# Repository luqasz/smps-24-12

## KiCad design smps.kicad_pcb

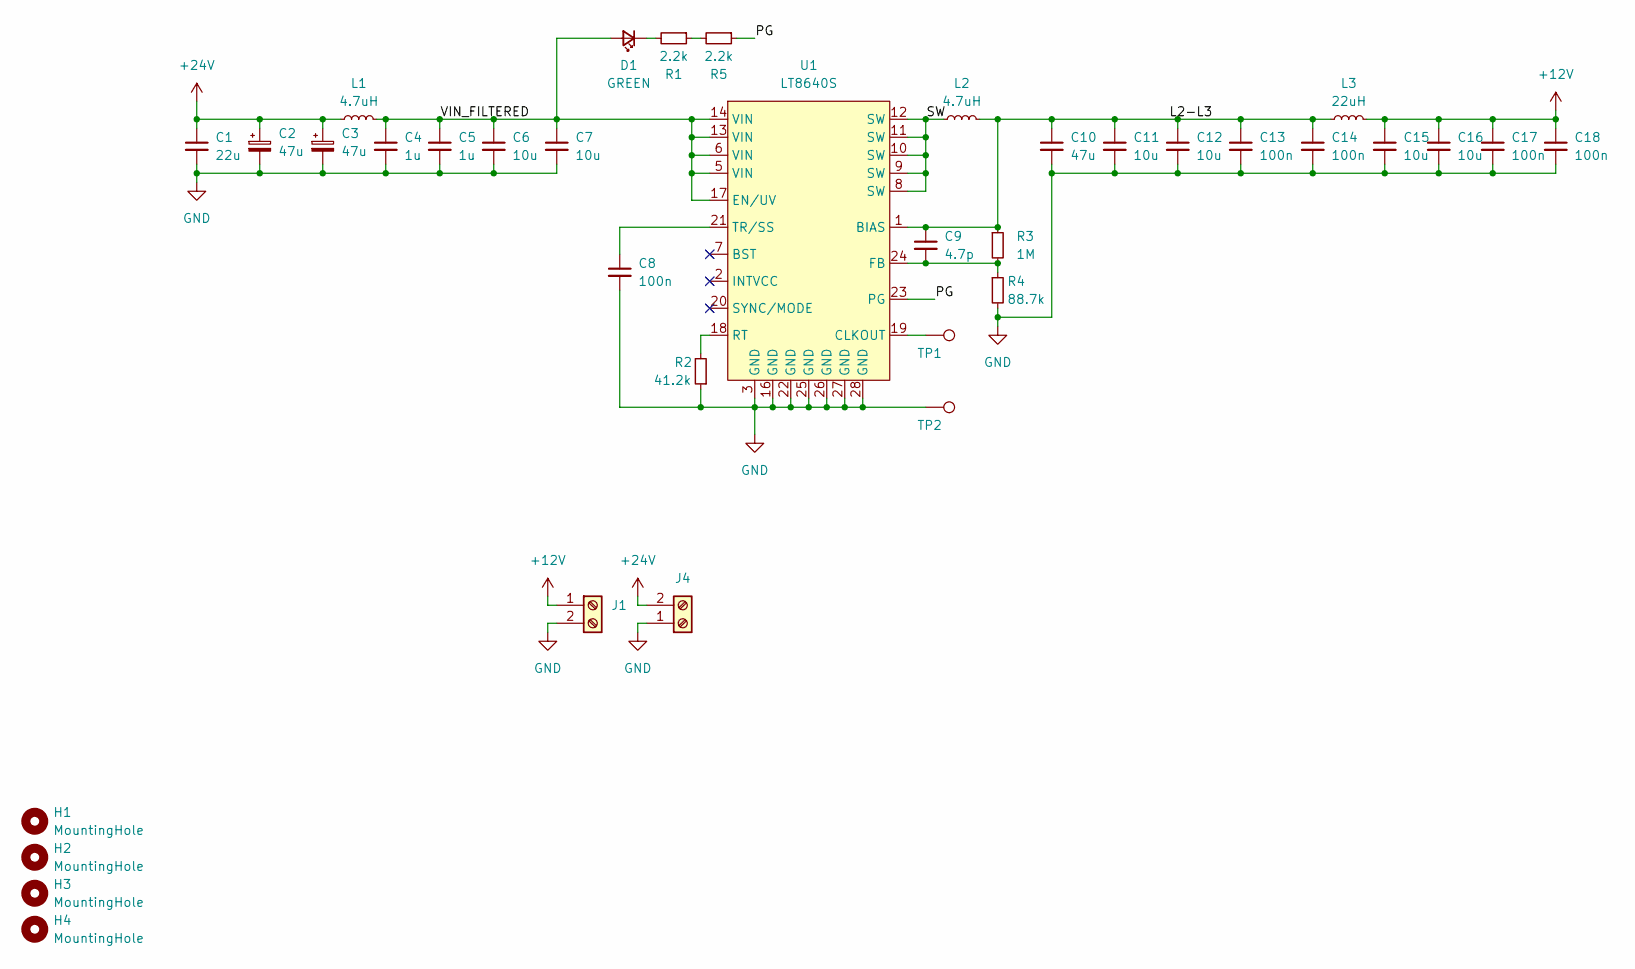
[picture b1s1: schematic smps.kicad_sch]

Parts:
C1: 22u; C_1206_3216Metric
C2, C3: 47u; CP_Elec_8x6.2
C4, C5: 1u; C_0805_2012Metric
C6, C7, C11, C12, C15, C16: 10u; C_1206_3216Metric
C8, C13, C14, C17, C18: 100n; C_0805_2012Metric
C9: 4.7p; R_0805_2012Metric
C10: 47u; C_1206_3216Metric
D1: GREEN; LED_0805_2012Metric
H1, H2, H3, H4: MountingHole; MountingHole_3.2mm_M3
J1, J4: Screw_Terminal_01x02; TerminalBlock_Phoenix_MKDS-1,5-2-5.08_1x02_P5.08mm_Horizont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
L1, L2: 4.7uH; L_Wuerth_WE-PD-Typ-LS_Handsoldering
L3: 22uH; L_Wuerth_WE-PD-Typ-LS_Handsoldering
R1, R5: 2.2k; R_0805_2012Metric
R2: 41.2k; R_0805_2012Metric
R3: 1M; R_0805_2012Metric
R4: 88.7k; R_0805_2012Metric
TP1, TP2: TestPoint; TestPoint_Pad_D1.0mm
U1: LT8640S; LQFN-24-4x4mm_P0.5mm_4EP_1.125mm

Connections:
+12V: C15.1, C16.1, C17.1, C18.1, J1.1, L3.2
+24V: C1.1, C2.1, C3.1, J4.2, L1.1
/L2-L3: C9.1, C10.1, C11.1, C12.1, C13.1, C14.1, L2.2, L3.1, R3.1, U1.1 (BIAS)
/PG: R5.1, U1.23 (PG)
/SW: L2.1, U1.8 (SW), U1.9 (SW), U1.10 (SW), U1.11 (SW), U1.12 (SW)
/VIN_FILTERED: C4.1, C5.1, C6.1, C7.1, D1.2 (A), L1.2, U1.5 (VIN), U1.6 (VIN), U1.13 (VIN), U1.14 (VIN), U1.17 (EN/UV)
GND: C1.2, C2.2, C3.2, C4.2, C5.2, C6.2, C7.2, C8.2, C10.2, C11.2, C12.2, C13.2, C14.2, C15.2, C16.2, C17.2, C18.2, J1.2, J4.1, R2.1, R4.2, TP2.1, U1.3 (GND), U1.16 (GND), U1.22 (GND), U1.25 (GND), U1.26 (GND), U1.27 (GND), U1.28 (GND)
unnamed: C8.1, U1.21 (TR/SS)
unnamed: C9.2, R3.2, R4.1, U1.24 (FB)
unnamed: D1.1 (K), R1.2
unnamed: R1.1, R5.2
unnamed: R2.2, U1.18 (RT)
unnamed: TP1.1, U1.19 (CLKOUT)

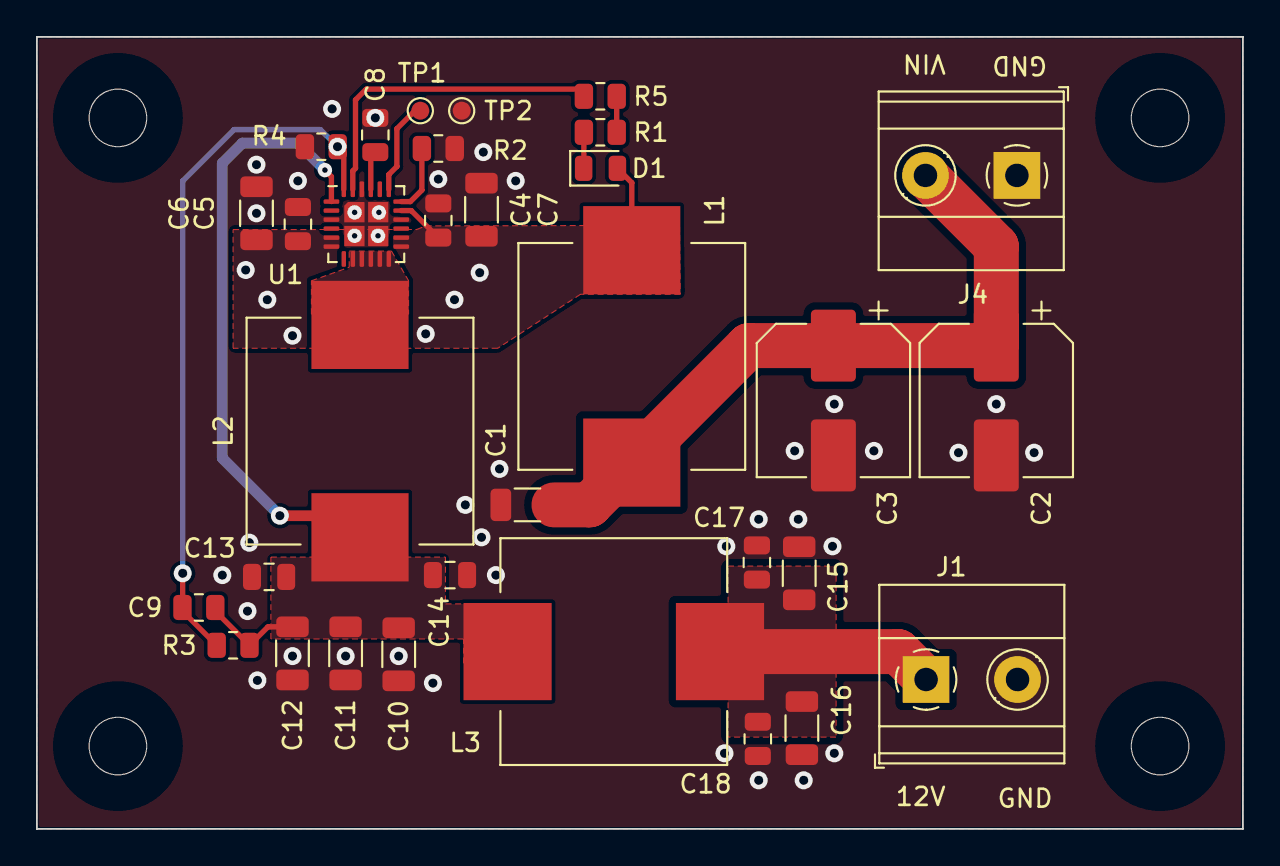
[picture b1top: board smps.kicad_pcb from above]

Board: 2 copper layers, 67.0 x 44.0 mm, 36 parts (0 on the bottom side), 13 nets.

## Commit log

2022-03-19 Update PCB layout
2022-04-04 Cosmetic updates
2022-04-18 Fix cap silkscreen
2022-04-18 Fix L1 input coil value
